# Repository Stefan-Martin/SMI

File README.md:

# self-mixing-interferometry
FYDP 2019-2020

Board schematics and PCB layouts are available under "Hardware", files are Ki-Cad.
Prototype fringe detection scripts and USB-Dux sampling code is available under "Scripts".

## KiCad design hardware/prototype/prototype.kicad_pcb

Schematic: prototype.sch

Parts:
C1, C2, C5: 0.1uF; CP_Radial_D5.0mm_P2.50mm
C3: 150pF; CP_Radial_D5.0mm_P2.50mm
C4: 10uF; CP_Radial_D5.0mm_P2.50mm
J1: OUTPUT probe; PinHeader_1x02_P2.54mm_Vertical
J2: BATT HIGH; PhoenixContact_MCV-G_02x3.50mm_Vertical
J3: OUTPUT; PhoenixContact_MCV-G_02x3.50mm_Vertical
J4: BATT LOW; PhoenixContact_MCV-G_02x3.50mm_Vertical
J5: LASER CONN; PhoenixContact_MCV-G_03x3.50mm_Vertical
R1: 165; R_Axial_DIN0207_L6.3mm_D2.5mm_P10.16mm_Horizontal
R2: 23.5K; R_Axial_DIN0207_L6.3mm_D2.5mm_P10.16mm_Horizontal
R3: 22K; R_Axial_DIN0207_L6.3mm_D2.5mm_P10.16mm_Horizontal
TP2: TIA voltage; TestPoint_THTPad_D2.0mm_Drill1.0mm
U1: TL082; DIP-8_W7.62mm
U2: LT1460-5; TO-92_Inline_Narrow_Oval

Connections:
+9V: C1.2, C5.1, J2.1, U1.8 (V+), U2.1
-9V: C2.2, J4.2, U1.4 (V-)
/5V: R1.2, U2.2
/LD_IN: J5.1, R1.1, U1.2 (-)
/PD_OUT: C3.2, J5.2, R3.2, U1.6 (-)
/TIA_HIGHPASS: C4.1, J1.1, J3.1
/TIA_OUT: C3.1, C4.2, R2.1, R3.1, TP2.1, U1.7
GND: C1.1, C2.1, C5.2, J1.2, J2.2, J3.2, J4.1, J5.3, R2.2, U1.1, U1.3 (+), U1.5 (+), U2.3

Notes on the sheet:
Input power (2x 9V batteries)
Op amp power rail

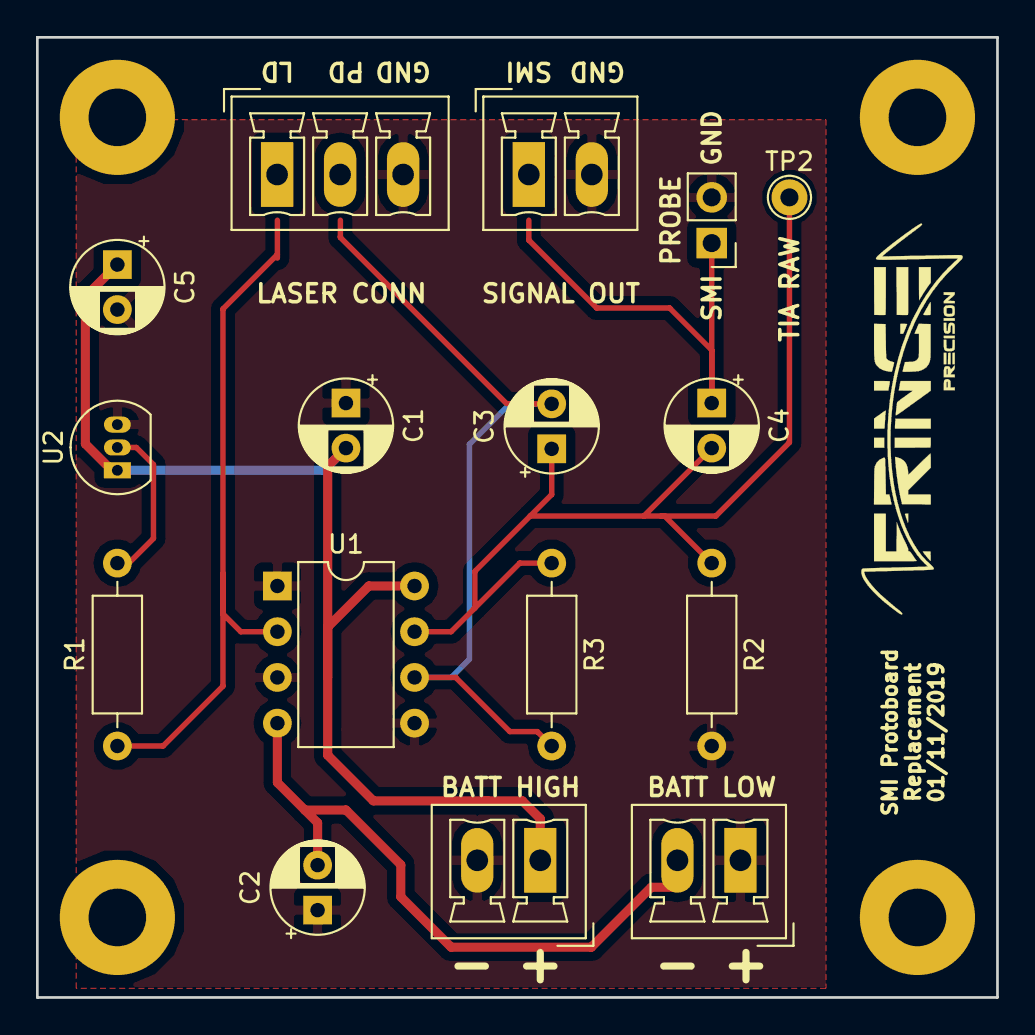
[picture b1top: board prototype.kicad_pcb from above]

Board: 2 copper layers, 53.3 x 53.3 mm, 20 parts (0 on the bottom side), 8 nets.

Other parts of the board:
H1, H2, H3, H4: MountingHole; MountingHole_3.2mm_M3_Pad

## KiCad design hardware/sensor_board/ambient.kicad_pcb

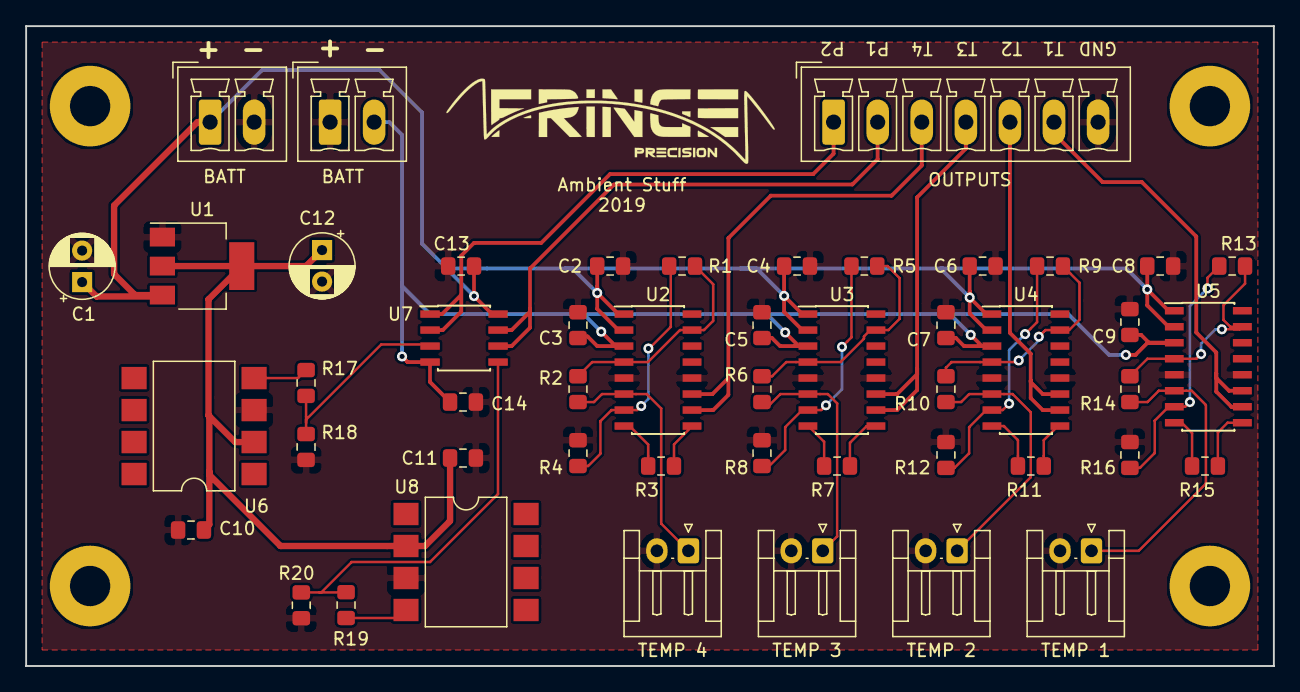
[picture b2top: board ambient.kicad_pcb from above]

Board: 2 copper layers, 99.1 x 50.8 mm, 53 parts (0 on the bottom side), 34 nets.

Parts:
C1: 10uF; CP_Radial_D5.0mm_P2.50mm
C2, C3, C4, C5, C6, C7, C8, C9, C10, C11, C13, C14: 0.1uF; C_0805_2012Metric_Pad1.15x1.40mm_HandSolder
C12: 22uF; CP_Radial_D5.0mm_P2.50mm
H1, H2, H3, H4: MountingHole; MountingHole_3.2mm_M3_Pad
J1: BATT+; PhoenixContact_MCV_1,5_2-G-3.5_1x02_P3.50mm_Vertical
J2: DAQ CONN; PhoenixContact_MCV_1,5_7-G-3.5_1x07_P3.50mm_Vertical
J3: BATT-; PhoenixContact_MCV_1,5_2-G-3.5_1x02_P3.50mm_Vertical
R1, R5, R9, R13: 330K; R_0805_2012Metric_Pad1.15x1.40mm_HandSolder
R2, R6, R10, R14: 1K1; R_0805_2012Metric_Pad1.15x1.40mm_HandSolder
R3, R7, R11, R15: 2K; R_0805_2012Metric_Pad1.15x1.40mm_HandSolder
R4, R8, R12, R16: 3K3; R_0805_2012Metric_Pad1.15x1.40mm_HandSolder
R17: 47K; R_0805_2012Metric_Pad1.15x1.40mm_HandSolder
R18: 8K2; R_0805_2012Metric_Pad1.15x1.40mm_HandSolder
R19: 470K; R_0805_2012Metric_Pad1.15x1.40mm_HandSolder
R20: 82K; R_0805_2012Metric_Pad1.15x1.40mm_HandSolder
TEMP 1, TEMP 2, TEMP 3, TEMP 4: RTD CONN; JST_EH_S02B-EH_1x02_P2.50mm_Horizontal
U1: AZ1117-5.0; SOT-223-3_TabPin2
U2, U3, U4, U5: INA125P; SOIC-16_3.9x9.9mm_Pitch1.27mm
U6, U8: MPXA6115A; SMDIP-8_W9.53mm
U7: TL082; SOIC-8_3.9x4.9mm_Pitch1.27mm

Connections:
+5V: C10.1, C11.1, C12.1, U1.2, U6.2, U8.2
+12V: C1.1, C2.1, C4.1, C6.1, C8.1, C13.2, J1.1, U1.3, U2.1, U2.2, U3.1, U3.2, U4.1, U4.2, U5.1, U5.2, U7.8
-12V: C3.1, C5.1, C7.1, C9.1, C14.2, J3.2, U2.3, U3.3, U4.3, U5.3, U7.4
/PRESSURE: J2.1, U7.1, U7.2
/PRESSURE_BK: J2.2, U7.6, U7.7
/RTD_AMP_1: J2.3, U2.10, U2.11
/RTD_AMP_2: J2.4, U3.10, U3.11
/RTD_AMP_3: J2.5, U4.10, U4.11
/RTD_AMP_4: J2.6, U5.10, U5.11
/Temperature/RTD+: R2.2, TEMP 4.1, U2.6
/sheet5DD1B4ED/RTD+: R10.2, TEMP 2.1, U4.6
/sheet5DD1B5A5/RTD+: R14.2, TEMP 1.1, U5.6
/sheet5DD1B435/RTD+: R6.2, TEMP 3.1, U3.6
/sheet5DD1C8A8/P_BK_RAW: R19.2, R20.1, U7.5
/sheet5DD1C8A8/P_RAW: R17.2, R18.1, U7.3
GND: C1.2, C2.2, C3.2, C4.2, C5.2, C6.2, C7.2, C8.2, C9.2, C10.2, C11.2, C12.2, C13.1, C14.1, J1.2, J2.7, J3.1, R4.2, R8.2, R12.2, R16.2, R18.2, R20.2, TEMP 1.2, TEMP 2.2, TEMP 3.2, TEMP 4.2, U1.1, U2.5, U2.12, U3.5, U3.12, U4.5, U4.12, U5.5, U5.12, U6.3, U8.3
unnamed: R1.1, R2.1, U2.4, U2.15
unnamed: R1.2, R4.1, U2.7
unnamed: R3.1, U2.8
unnamed: R3.2, U2.9
unnamed: R5.1, R6.1, U3.4, U3.15
unnamed: R5.2, R8.1, U3.7
unnamed: R7.1, U3.8
unnamed: R7.2, U3.9
unnamed: R9.1, R10.1, U4.4, U4.15
unnamed: R11.1, U4.8
unnamed: R11.2, U4.9
unnamed: R9.2, R12.1, U4.7
unnamed: R13.1, R14.1, U5.4, U5.15
unnamed: R13.2, R16.1, U5.7
unnamed: R15.1, U5.8
unnamed: R15.2, U5.9
unnamed: R17.1, U6.4
unnamed: R19.1, U8.4

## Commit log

2019-04-16 add gitignore
2019-04-16 peak finding
2019-07-05 signal simulation from paper
2019-07-05 Fix spacing and naming in smi simulator
2019-07-05 displacement plotting script
2019-07-07 jump and reversal point calculation
2019-07-07 motion direction
2019-07-07 peak and valley finding half done, missing peaks and valleys immediately before direction changes
2019-07-08 peak and valley detection working
2019-07-08 phase unwrapping mostly working
2019-07-10 phase unwrapping done
2019-07-10 one last phase unwrapping bug to squash...
2019-07-10 first perfect reconstruction
2019-07-10 clean up plotting code
2019-07-11 Added DAQ readout script
2019-09-27 Add preliminary analog schematics
    Todo: fix grounding, add more RTD amps if needed
2019-10-31 Refine analog circuitry
2019-10-31 Nail down component values for filter
2019-11-13 Add schematic + layout for protoboard clone
2019-11-17 Save filters and whatnot before the culling
    TODO:
    - split ambient and SMI circuitry onto different boards
    - kill off the pseudoground and use lipo batteries instead
2019-11-17 Update prototype PCB
2019-11-17 Split monolithic board into ambient and smi
2019-11-17 Add layout for ambient sensors
2019-11-18 Finish routing on sensor board
2020-01-09 async script
2020-01-09 formatting
2020-01-09 Added gaussian white noise option
2020-01-09 removed csv output
2020-01-09 Added simulated signals and copied a separate basic plot function
2020-01-13 stage scripts
2020-01-16 some code
2020-01-18 work
2020-01-29 raw data capture
2020-01-29 code
2020-01-30 proto fringe detection filter
2020-01-30 cleaned up old files
2020-02-05 New fringe test
2020-02-06 reduced threshold on jump check to be better
2020-02-14 Naming and metadata
2020-02-15 New file format
2020-02-15 disgusting lowpass
2020-02-17 New signal
2020-02-25 wavelet methods
2020-02-26 Audio demo
2020-02-26 Scrolling wavelet
2020-03-03 temp cal
2020-03-03 Temp calibration curves
2020-06-07 Final revision
    Including future circuits for voltage offset, etc
2020-06-07 Cleaned up for release
2020-06-07 Created Readme
2020-06-07 Added sensor_board
